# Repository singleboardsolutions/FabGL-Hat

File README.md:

# FabGL-Hat
 Obsidian ESP32 hat for FabGL, 2 bpp color and PS/2 Mouse and keyboard

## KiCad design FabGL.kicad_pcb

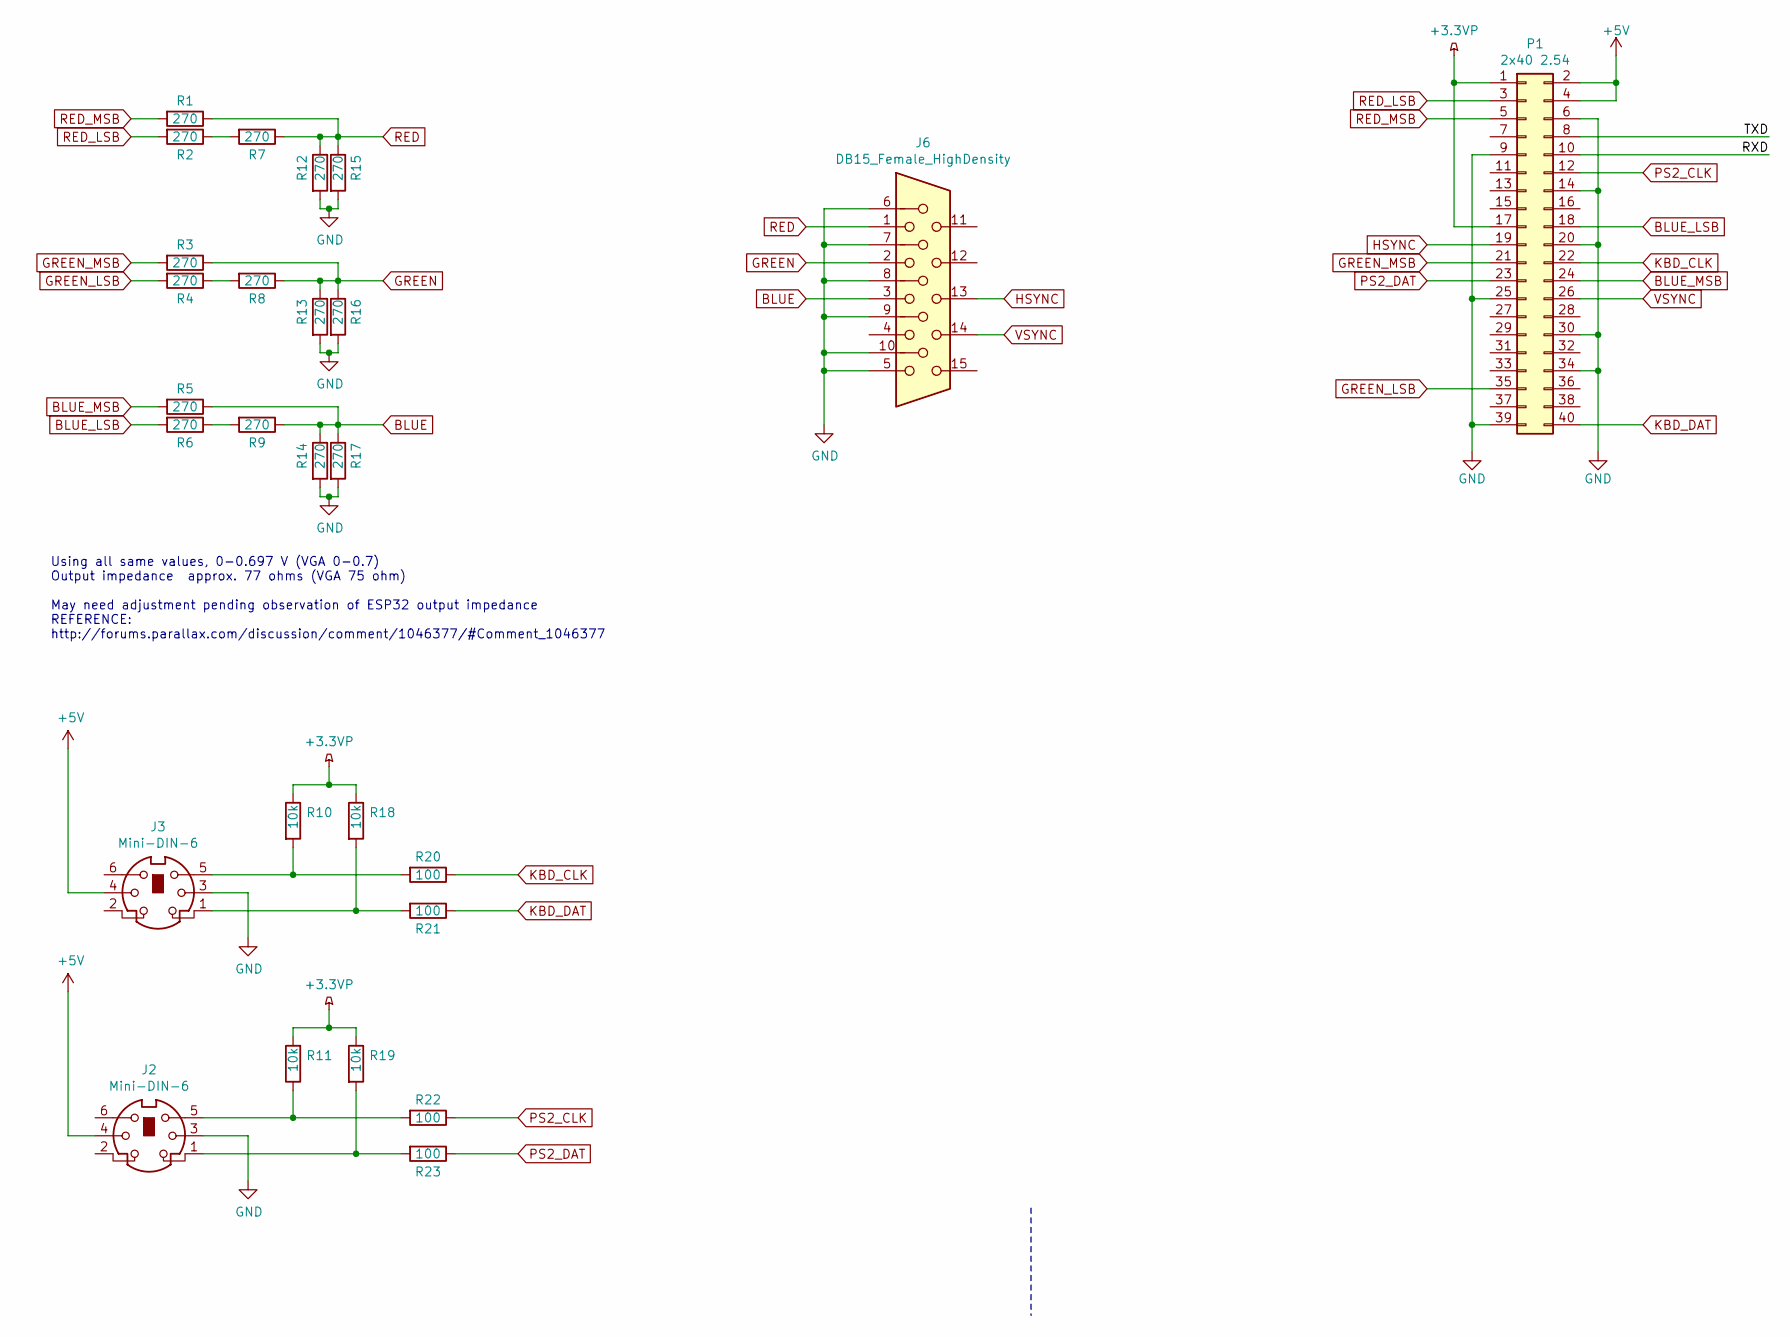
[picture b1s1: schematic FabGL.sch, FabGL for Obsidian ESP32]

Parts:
J2, J3: Mini-DIN-6; mini-din-6-CUI_MD60S
J6: DB15_Female_HighDensity; DSUB-15-HD_Female_Horizontal_P2.29x1.98mm_EdgePinOffset3.03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
P1: 2x40 2.54; Socket_Strip_Straight_2x20_Pitch2.54mm
R1, R2, R3, R4, R5, R6, R7, R8, R9, R12, R13, R14, R15, R16, R17: 270; R_0603
R10, R11, R18, R19: 10k; R_0603
R20, R21, R22, R23: 100; R_0603

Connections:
+3.3VP: P1.1, P1.17, R10.1, R11.2, R18.1, R19.1
+5V: J2.4, J3.4, P1.2, P1.4
/RXD: P1.10
/TXD: P1.8
BLUE: J6.3, R5.1, R9.1, R14.1, R17.1
BLUE_LSB: P1.18, R6.2
BLUE_MSB: P1.24, R5.2
GND: J2.3, J3.3, J6.5, J6.6, J6.7, J6.8, J6.9, J6.10, P1.6, P1.9, P1.14, P1.20, P1.25, P1.30, P1.34, P1.39, R12.2, R13.2, R14.2, R15.2, R16.2, R17.2
GREEN: J6.2, R3.1, R8.1, R13.1, R16.1
GREEN_LSB: P1.35, R4.2
GREEN_MSB: P1.21, R3.2
HSYNC: J6.13, P1.19
KBD_CLK: P1.22, R20.1
KBD_DAT: P1.40, R21.1
unnamed: J2.1, R19.2, R23.2
unnamed: J2.5, R11.1, R22.2
unnamed: J3.1, R18.2, R21.2
unnamed: J3.5, R10.2, R20.2
unnamed: R2.1, R7.2
unnamed: R4.1, R8.2
unnamed: R6.1, R9.2
PS2_CLK: P1.12, R22.1
PS2_DAT: P1.23, R23.1
RED: J6.1, R1.1, R7.1, R12.1, R15.1
RED_LSB: P1.3, R2.2
RED_MSB: P1.5, R1.2
VSYNC: J6.14, P1.26

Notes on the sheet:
Using all same values, 0-0.697 V (VGA 0-0.7) Output impedance approx. 77 ohms (VGA 75 ohm) May need adjustment pending observation of ESP32 output impedance REFERENCE: http://forums.parallax.com/discussion/comment/1046377/#Comment_1046377

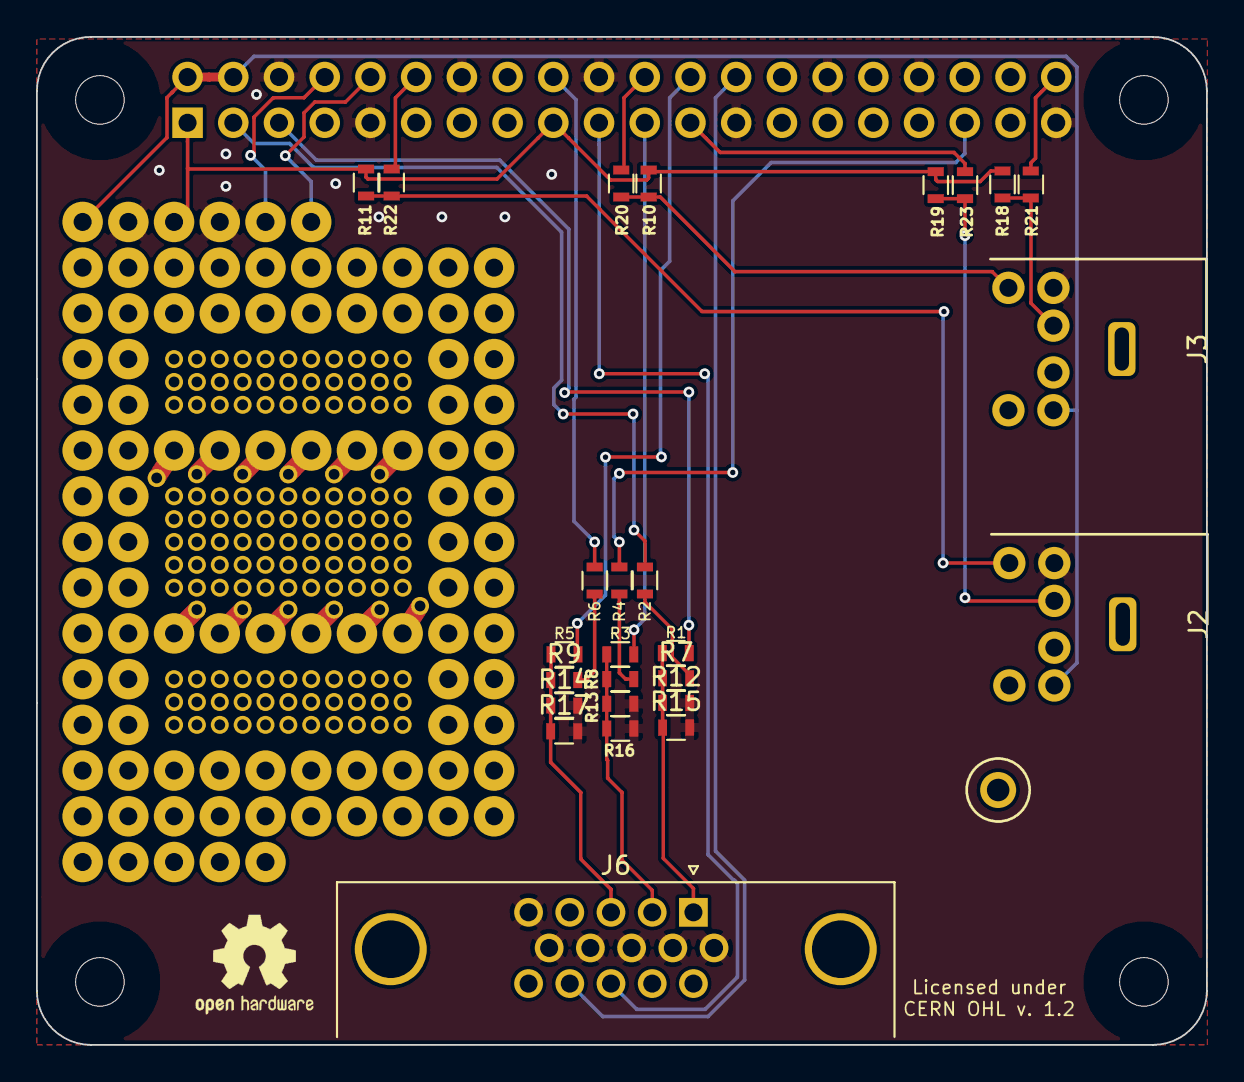
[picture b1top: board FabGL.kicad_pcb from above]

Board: 2 copper layers, 65.0 x 56.0 mm, 32 parts (1 on the bottom side), 25 nets.

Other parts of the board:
MK1, MK2, MK3, MK4: M2.5; MountingHole_2.7mm_M2.5
Ring 2: Test_Point; Test_Point_Keystone_5010-5014_Multipurpose

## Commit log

2019-07-17 Initial Commit
    First commit, extremely preliminary
2019-07-17 Update README.md
    Fix Typo, improve description
2019-07-17 License and PCB adjustments
    Added CERN OHL 1.2
    Added Proto Area for both DIP and SOIC
2019-07-18 gerbers
    adding gerbers for ordering from PCB houses.
2019-07-24 Pin swap
    Fix pins so the board will boot, correction of error on use of strapping pins

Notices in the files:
FabGL.kicad_pcb:
This document describes Open Hardware and is licensed under the CERN OHL v. 1.2
Copyright Thomas McKahan 2019
CERN OHL v. 1.2
You may redistribute and modify this documentation under the
terms of the CERN OHL v.1.2. This document is distributed
FabGL.sch:
Copyright 2019 Thomas McKahan
Copyright 2019 Single Board Solutions, LLC
